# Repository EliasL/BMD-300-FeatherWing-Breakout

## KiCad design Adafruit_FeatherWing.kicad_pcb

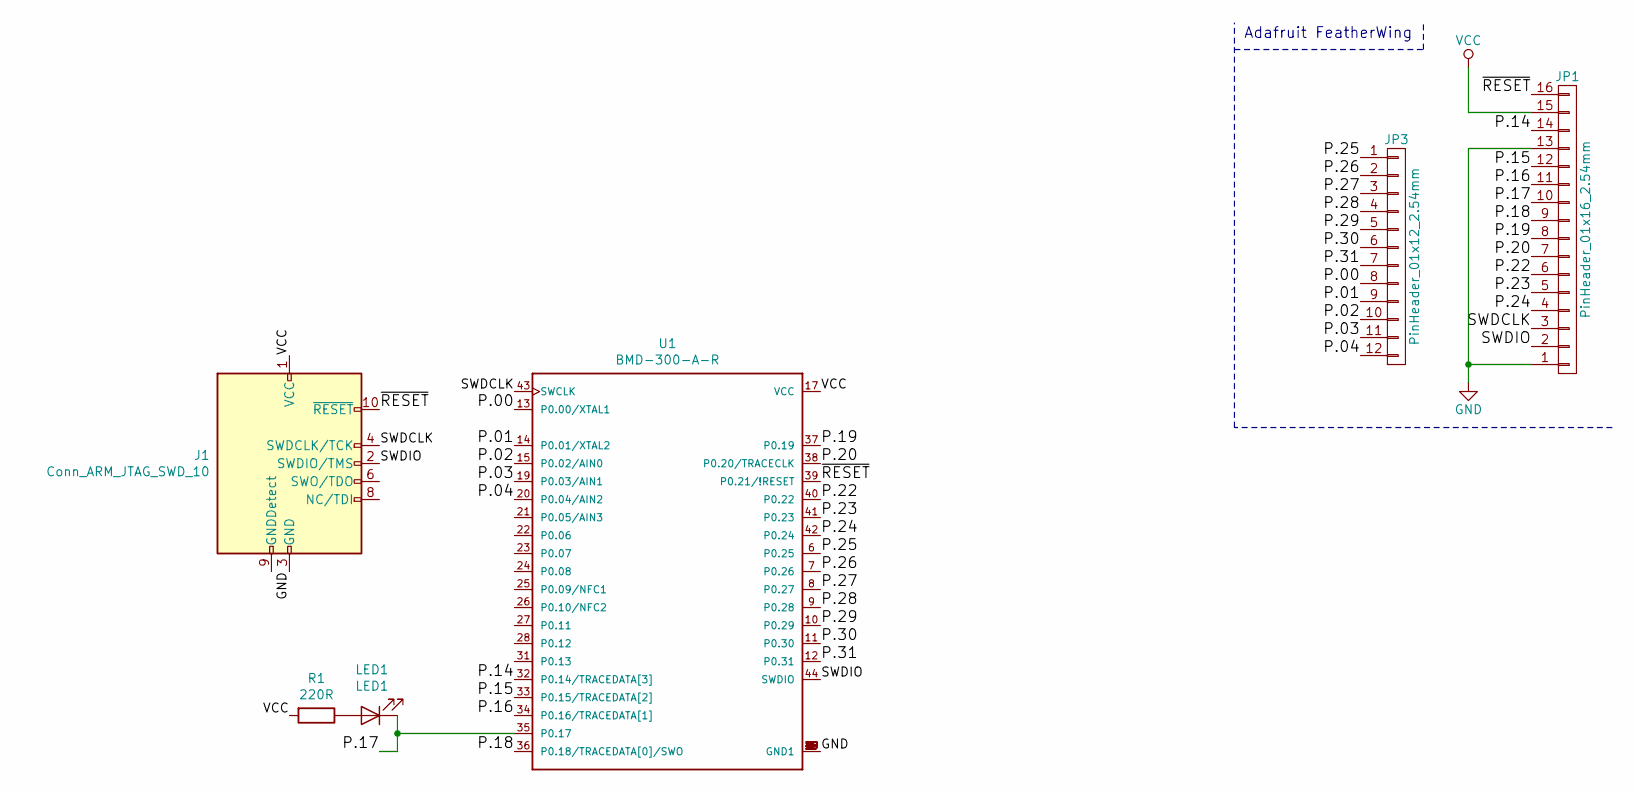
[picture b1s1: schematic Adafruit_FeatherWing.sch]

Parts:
J1: Conn_ARM_JTAG_SWD_10; PinHeader_2x05_P1.27mm_Vertical_SMD
JP1: PinHeader_01x16_2.54mm; PinSocket_1x16_P2.54mm_Vertical
JP3: PinHeader_01x12_2.54mm; PinSocket_1x12_P2.54mm_Vertical
LED1: LED1; LED_0603_1608Metric
R1: 220R; R_0603_1608Metric
U1: BMD-300-A-R; RIGADO_BMD-300-A-R

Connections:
/P.00: JP3.8, U1.13 (P0.00/XTAL1)
/P.01: JP3.9, U1.14 (P0.01/XTAL2)
/P.02: JP3.10, U1.15 (P0.02/AIN0)
/P.03: JP3.11, U1.19 (P0.03/AIN1)
/P.04: JP3.12, U1.20 (P0.04/AIN2)
/P.14: JP1.14, U1.32 (P0.14/TRACEDATA[3])
/P.15: JP1.12, U1.33 (P0.15/TRACEDATA[2])
/P.16: JP1.11, U1.34 (P0.16/TRACEDATA[1])
/P.17: JP1.10, LED1.1 (K), U1.35 (P0.17)
/P.18: JP1.9, U1.36 (P0.18/TRACEDATA[0]/SWO)
/P.19: JP1.8, U1.37 (P0.19)
/P.20: JP1.7, U1.38 (P0.20/TRACECLK)
/P.22: JP1.6, U1.40 (P0.22)
/P.23: JP1.5, U1.41 (P0.23)
/P.24: JP1.4, U1.42 (P0.24)
/P.25: JP3.1, U1.6 (P0.25)
/P.26: JP3.2, U1.7 (P0.26)
/P.27: JP3.3, U1.8 (P0.27)
/P.28: JP3.4, U1.9 (P0.28)
/P.29: JP3.5, U1.10 (P0.29)
/P.30: JP3.6, U1.11 (P0.30)
/P.31: JP3.7, U1.12 (P0.31)
/SWDCLK: J1.4 (SWDCLK/TCK), JP1.3, U1.43 (SWCLK)
/SWDIO: J1.2 (SWDIO/TMS), JP1.2, U1.44 (SWDIO)
/~RESET: J1.10 (~RESET~), JP1.16, U1.39 (P0.21/!RESET)
GND: J1.3 (GND), J1.5 (GND), JP1.1, JP1.13, U1.1 (GND1), U1.2 (GND1), U1.3 (GND1), U1.4 (GND1), U1.5 (GND1), U1.16 (GND1), U1.18 (GND1), U1.29 (GND1), U1.30 (GND1), U1.45 (GND1), U1.46 (GND1), U1.47 (GND1)
unnamed: LED1.2 (A), R1.1
VCC: J1.1 (VCC), JP1.15, R1.2, U1.17 (VCC)

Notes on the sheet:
Adafruit FeatherWing

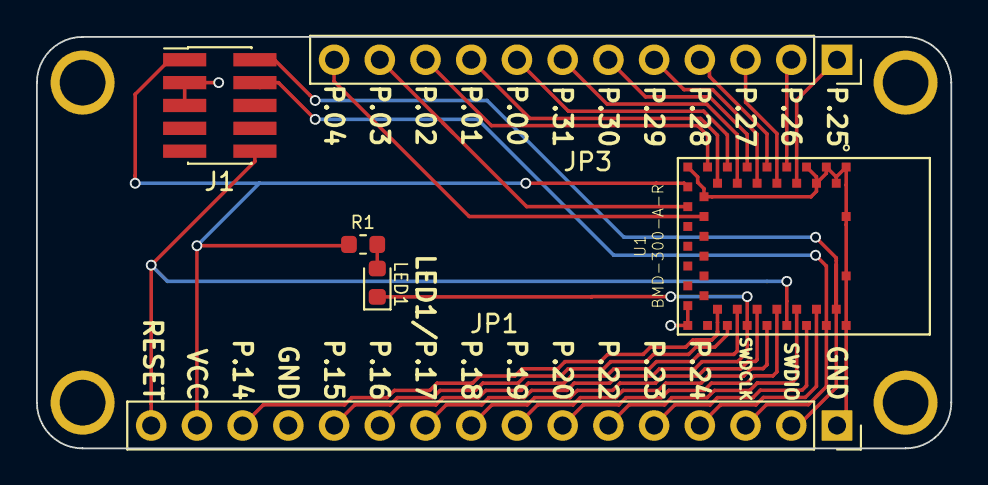
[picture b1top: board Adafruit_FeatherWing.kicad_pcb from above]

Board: 2 copper layers, 50.8 x 22.9 mm, 7 parts (0 on the bottom side), 28 nets.

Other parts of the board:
PCB**: VAL**; PCB_FeatherWing
